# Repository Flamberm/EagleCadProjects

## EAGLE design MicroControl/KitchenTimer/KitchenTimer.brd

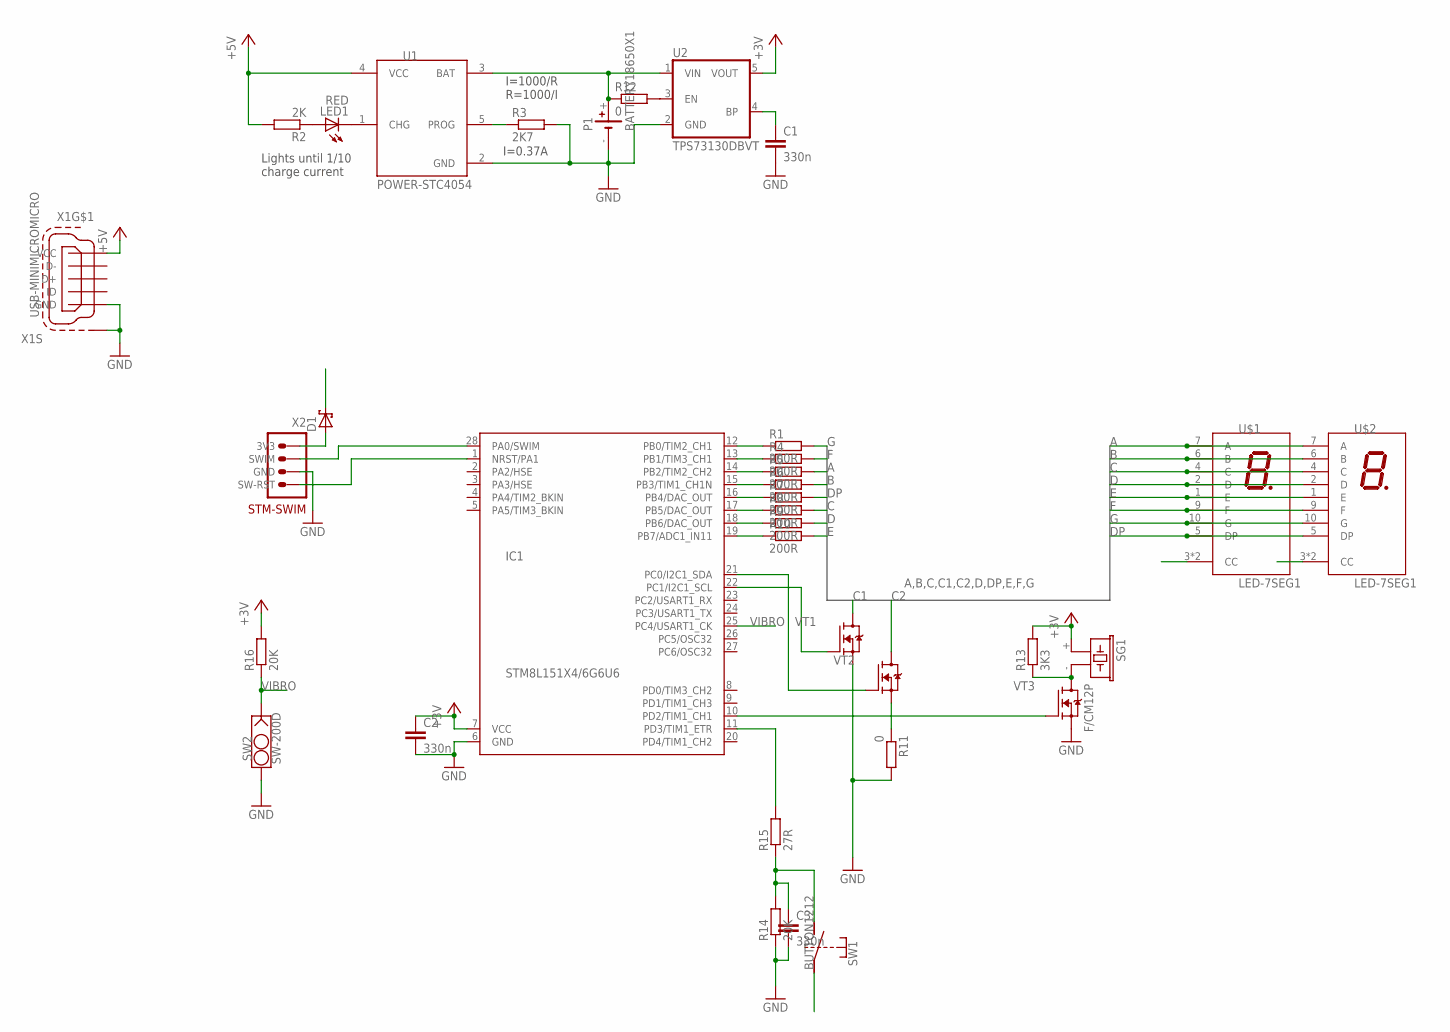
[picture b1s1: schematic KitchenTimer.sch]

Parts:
C1, C2, C3: 330n; CAP1206
D1: DIODE-SH_SOD523; SODFL1608X65
IC1: STM8L151X4/6G6U6; QFN28
LED1: RED; LED1206
P1: BATTERY18650X1; 18650X1_HOLDER
R1, R4, R5, R6, R7, R8, R9, R10: 200R; RESC2012X50
R2: 2K; RESC2012X50
R3: 2K7; RESC2012X50
R11, R12: 0; RESC2012X50
R13: 3K3; RESC3216X60
R14, R16: 20K; RESC3216X60
R15: 27R; RESC3216X60
SG1: F/CM12P
SW1: BUTTON1212; B3F-40XX
SW2: SW-200D
U1: POWER-STC4054; SOT95P280X145-5
U2: TPS73130DBVT; SOT95P280X145-5
U$1, U$2: LED-7SEG1
VT1, VT2, VT3: FET-NSOT-23; SOT95P240X115-3
X1: USB-MINIMICROMICRO; USB-B-MICRO-SMD
X2: STM-SWIMPOGOPADS; SWIM-PADS-1.27

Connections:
+3V: C2.1, D1.1 (C), IC1.7 (VCC), R13.2, R16.2, SG1.+ (1), SW1.1, SW1.2 (1), U2.5 (VOUT)
+5V: R2.2, U1.4 (VCC), X1.VBUS (VCC)
A: R5.2, U$1.7 (A), U$2.7 (A)
B: R6.2, U$1.6 (B), U$2.6 (B)
C: R8.2, U$1.4 (C), U$2.4 (C)
C1: U$1.3 (CC), U$1.8 (CC), VT1.3 (D)
C2: U$2.3 (CC), U$2.8 (CC), VT2.3 (D)
D: R9.2, U$1.2 (D), U$2.2 (D)
DP: R7.2, U$1.5 (DP), U$2.5 (DP)
E: R10.2, U$1.1 (E), U$2.1 (E)
F: R4.2, U$1.9 (F), U$2.9 (F)
G: R1.2, U$1.10 (G), U$2.10 (G)
GND: C1.2, C2.2, C3.2, IC1.6 (GND), P1.-, R3.2, R11.2, R14.1, SW2.S, U1.2 (GND), U2.2 (GND), VT1.2 (S), VT3.2 (S), X1.GND, X1.SHIELD1 (S1), X1.SHIELD2 (S1), X1.SHIELD3 (S1), X2.P$3 (GND)
unnamed: LED1.C, U1.1 (CHG)
unnamed: LED1.A, R2.1
unnamed: IC1.12 (PB0/TIM2_CH1), R1.1
unnamed: IC1.13 (PB1/TIM3_CH1), R4.1
unnamed: R3.1, U1.5 (PROG)
unnamed: IC1.14 (PB2/TIM2_CH2), R5.1
unnamed: P1.+, R12.1, U1.3 (BAT), U2.1 (VIN)
unnamed: IC1.15 (PB3/TIM1_CH1N), R6.1
unnamed: IC1.16 (PB4/DAC_OUT), R7.1
unnamed: IC1.17 (PB5/DAC_OUT), R8.1
unnamed: IC1.18 (PB6/DAC_OUT), R9.1
unnamed: IC1.19 (PB7/ADC1_IN11), R10.1
unnamed: IC1.22 (PC1/I2C1_SCL), VT1.1 (G)
unnamed: IC1.21 (PC0/I2C1_SDA), VT2.1 (G)
unnamed: R11.1, VT2.2 (S)
unnamed: R12.2, U2.3 (EN)
unnamed: C1.1, U2.4 (BP)
unnamed: R13.1, SG1.- (2), VT3.3 (D)
unnamed: IC1.10 (PD2/TIM1_CH1), VT3.1 (G)
unnamed: C3.1, R14.2, R15.1, SW1.3 (2), SW1.4 (2)
unnamed: IC1.11 (PD3/TIM1_ETR), R15.2
unnamed: IC1.28 (PA0/SWIM), X2.P$2 (SWIM)
unnamed: IC1.1 (NRST/PA1), X2.P$4 (SW-RST)
unnamed: D1.2 (A), X2.P$1 (3V3)
VIBRO: IC1.25 (PC4/USART1_CK), R16.1, SW2.G

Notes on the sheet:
I=1000/R R=1000/I
I=0.37A
Lights until 1/10 charge current

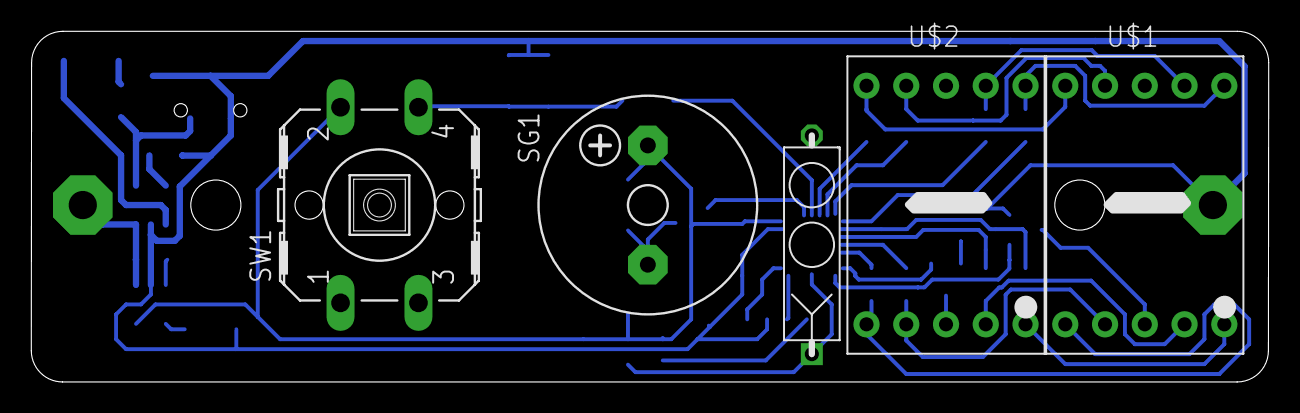
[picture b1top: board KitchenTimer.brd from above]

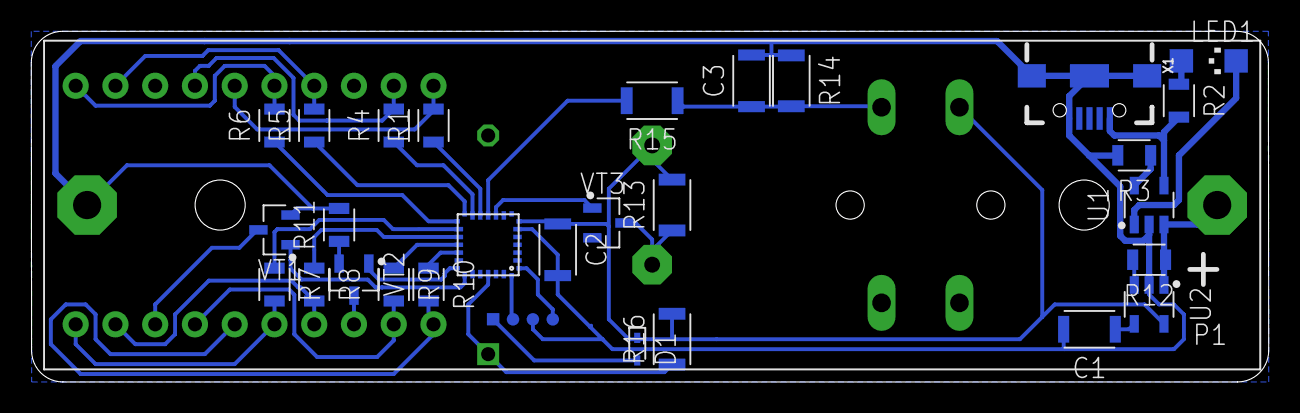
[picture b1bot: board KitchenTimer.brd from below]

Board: 2 copper layers, 79.1 x 22.4 mm, 35 parts (30 on the bottom side), 38 nets.

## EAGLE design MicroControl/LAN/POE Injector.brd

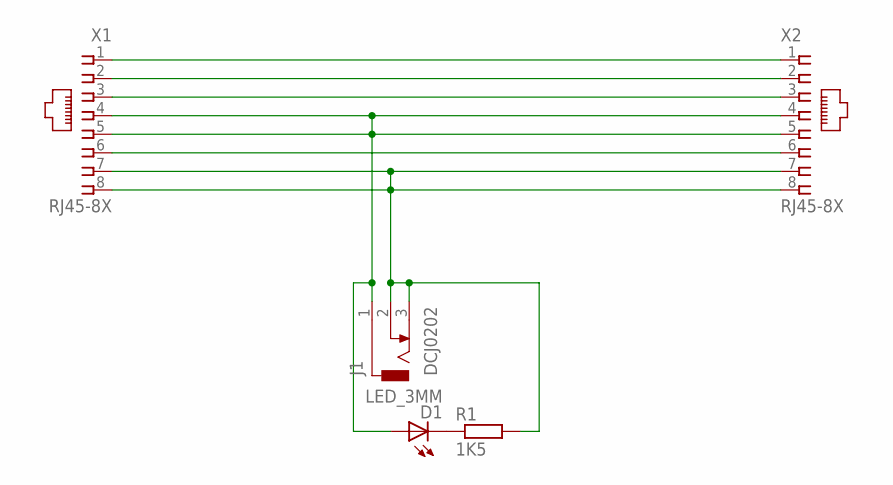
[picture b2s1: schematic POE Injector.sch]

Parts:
D1: LED_3MM; LED3MM
J1: DCJ0202
R1: 1K5; R1206
X1, X2: RJ45-8X; RJ45-NO-SHIELD

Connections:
unnamed: X1.1, X2.1
unnamed: X1.2, X2.2
unnamed: X1.3, X2.3
unnamed: X1.6, X2.6
unnamed: J1.2, J1.3, R1.2, X1.7, X1.8, X2.7, X2.8
unnamed: D1.A, J1.1, X1.4, X1.5, X2.4, X2.5
unnamed: D1.K (C), R1.1

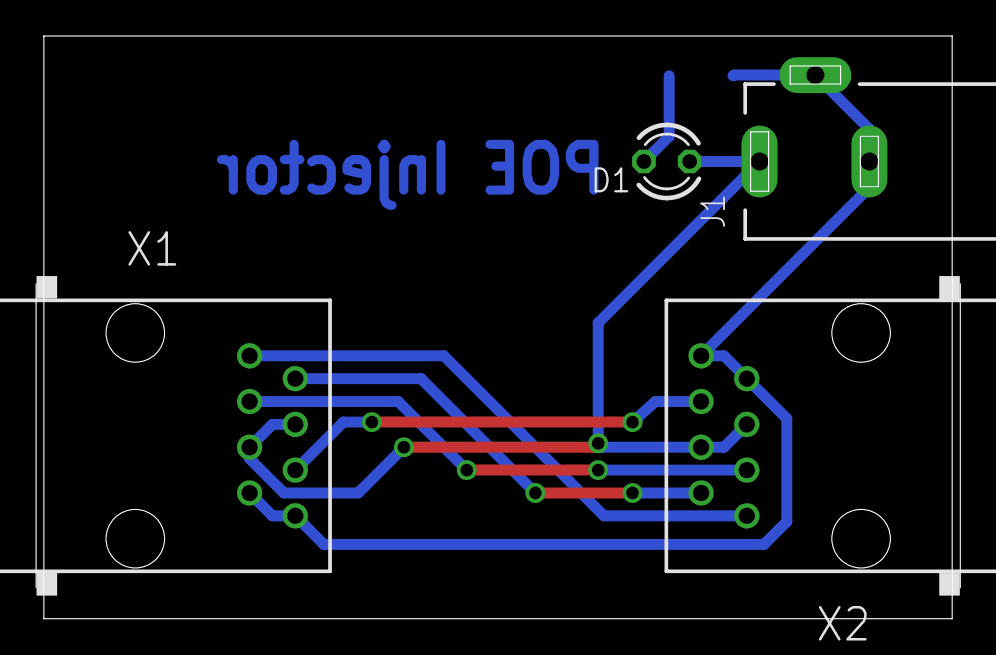
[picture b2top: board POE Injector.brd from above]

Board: 2 copper layers, 50.5 x 32.4 mm, 5 parts (1 on the bottom side), 7 nets.

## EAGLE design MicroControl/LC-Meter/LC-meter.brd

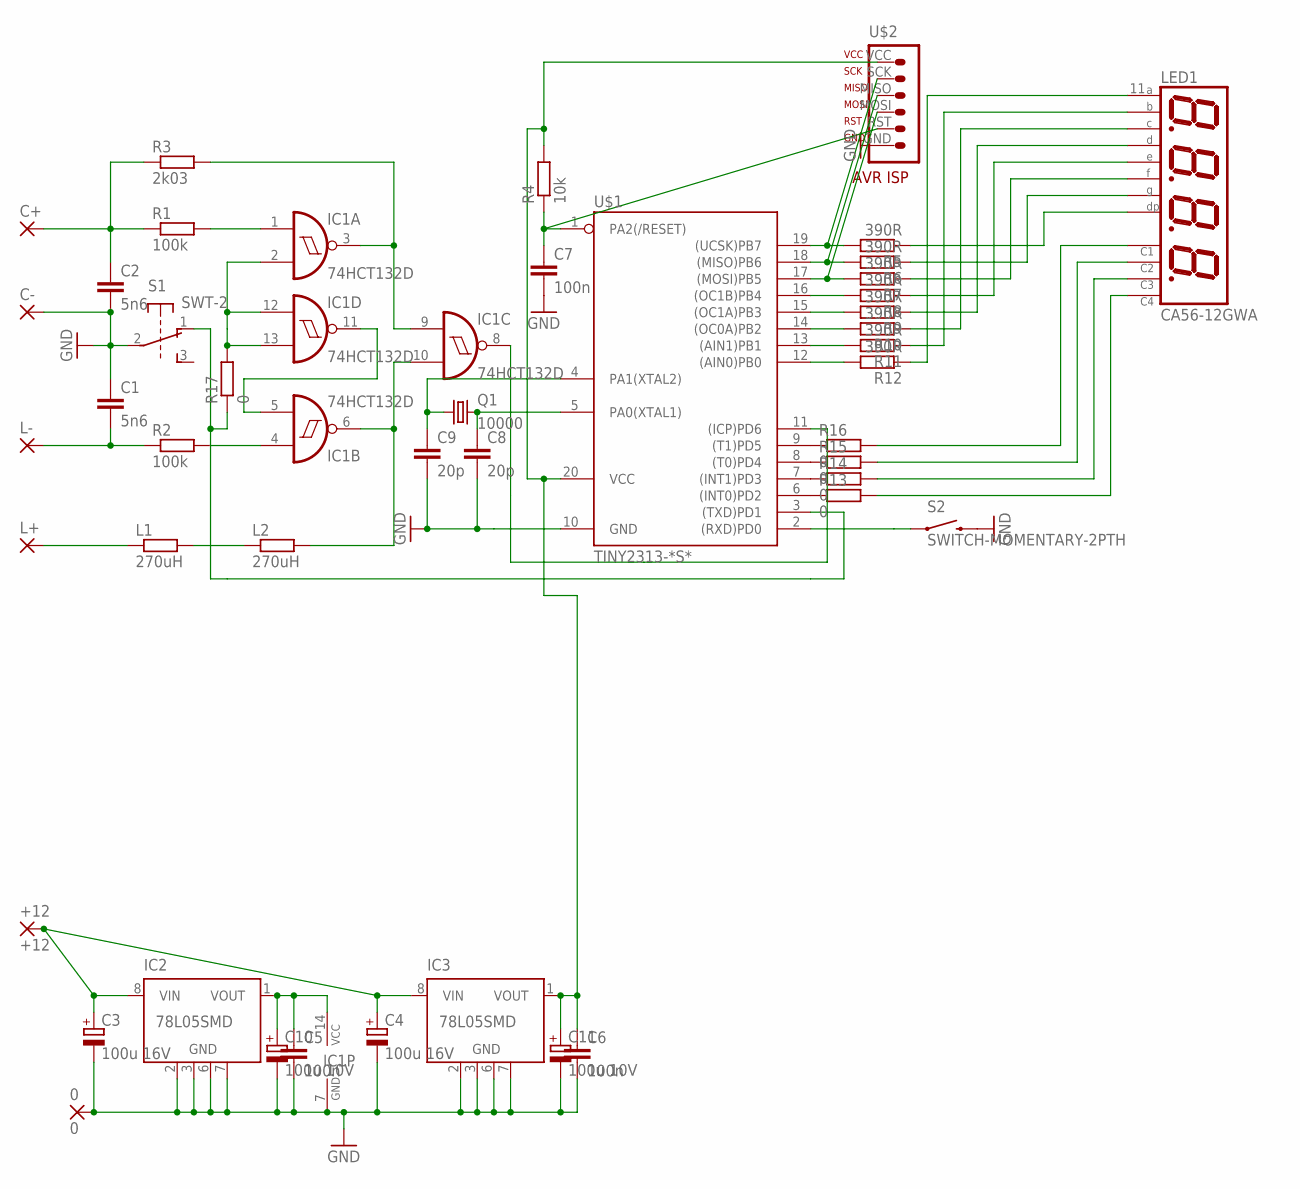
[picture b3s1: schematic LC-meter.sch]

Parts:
0: 0; 3,17/1,1
+12: +12; 3,17/1,1
C1, C2: 5n6; C0805
C3, C4: 100u 16V; E2,5-7
C5, C6, C7: 100n; C0805
C8, C9: 20p; C1206
C10, C11: 100u 10V; E2,5-7
C+: 3,17/1,1
C-: 3,17/1,1
IC1: 74HCT132D; SO14
IC2, IC3: 78L05SMD; SO08
L1, L2: 270uH; R1210
L+: 3,17/1,1
L-: 3,17/1,1
LED1: CA56-12GWA; 0,56_4X7SEG_LED
Q1: 10000; HC49/S
R1, R2: 100k; R1206
R3: 2k03; R1206
R4: 10k; R1206
R5, R6, R7, R8, R9, R10, R11, R12: 390R; R1206
R13, R14, R15, R16, R17: 0; R1206
S1: SWT-2
S2: SWITCH-MOMENTARY-2PTH; TACTILE-PTH
U$1: TINY2313-*S*; SO20L$
U$2: AVR-ISP-6-ROW

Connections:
GND: 0.1, C1.1, C2.2, C3.-, C4.-, C5.2, C6.2, C7.2, C8.2, C9.2, C10.-, C11.-, C-.1, IC1.7 (GND), IC2.2 (GND), IC2.3 (GND), IC2.6 (GND), IC2.7 (GND), IC3.2 (GND), IC3.3 (GND), IC3.6 (GND), IC3.7 (GND), S1.2, S2.3 (2), U$1.10 (GND), U$2.GND
unnamed: IC1.8 (O), U$1.11 ((ICP)PD6)
unnamed: R17.1, S1.1, U$1.3 ((TXD)PD1)
unnamed: IC1.5 (I1), IC1.11 (O)
unnamed: IC1.6 (O), IC1.10 (I1), L2.2
unnamed: IC1.3 (O), IC1.9 (I0), R3.2
unnamed: IC1.1 (I0), R1.2
unnamed: IC1.4 (I0), R2.2
unnamed: C1.2, L-.1, R2.1
unnamed: C2.1, C+.1, R1.1, R3.1
unnamed: L1.1, L+.1
unnamed: L1.2, L2.1
unnamed: +12.1, C3.+, C4.+, IC2.8 (VIN), IC3.8 (VIN)
unnamed: R5.2, U$1.19 ((UCSK)PB7), U$2.SCK
unnamed: R13.1, U$1.6 ((INT0)PD2)
unnamed: C6.1, C11.+, IC3.1 (VOUT), R4.2, U$1.20 (VCC), U$2.VCC
unnamed: C5.1, C10.+, IC1.14 (VCC), IC2.1 (VOUT)
unnamed: R6.2, U$1.18 ((MISO)PB6), U$2.MISO
unnamed: C7.1, R4.1, U$1.1 (PA2(/RESET)), U$2.RST
unnamed: C8.1, Q1.2, U$1.5 (PA0(XTAL1))
unnamed: C9.1, Q1.1, U$1.4 (PA1(XTAL2))
unnamed: S2.1, U$1.2 ((RXD)PD0)
unnamed: R7.2, U$1.17 ((MOSI)PB5), U$2.MOSI
unnamed: R8.2, U$1.16 ((OC1B)PB4)
unnamed: R9.2, U$1.15 ((OC1A)PB3)
unnamed: R10.2, U$1.14 ((OC0A)PB2)
unnamed: R11.2, U$1.13 ((AIN1)PB1)
unnamed: R12.2, U$1.12 ((AIN0)PB0)
unnamed: LED1.11 (A), R12.1
unnamed: LED1.7 (B), R11.1
unnamed: LED1.4 (C), R10.1
unnamed: LED1.2 (D), R9.1
unnamed: LED1.1 (E), R8.1
unnamed: LED1.10 (F), R7.1
unnamed: LED1.5 (G), R6.1
unnamed: LED1.3 (DP), R5.1
unnamed: LED1.12 (A1), R16.2
unnamed: LED1.9 (A2), R15.2
unnamed: LED1.8 (A3), R14.2
unnamed: LED1.6 (A4), R13.2
unnamed: R14.1, U$1.7 ((INT1)PD3)
unnamed: R15.1, U$1.8 ((T0)PD4)
unnamed: R16.1, U$1.9 ((T1)PD5)
unnamed: IC1.2 (I1), IC1.12 (I0), IC1.13 (I1), R17.2

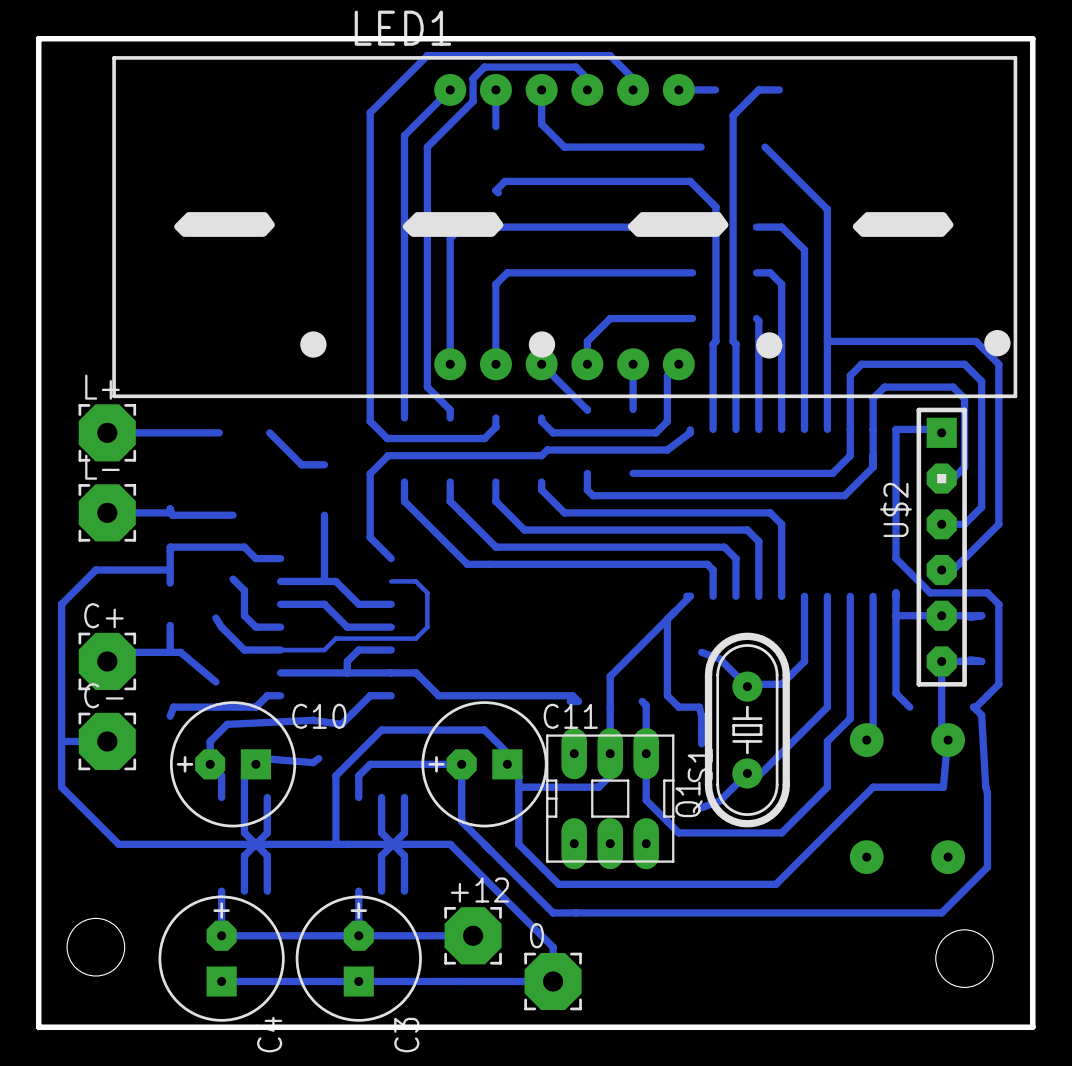
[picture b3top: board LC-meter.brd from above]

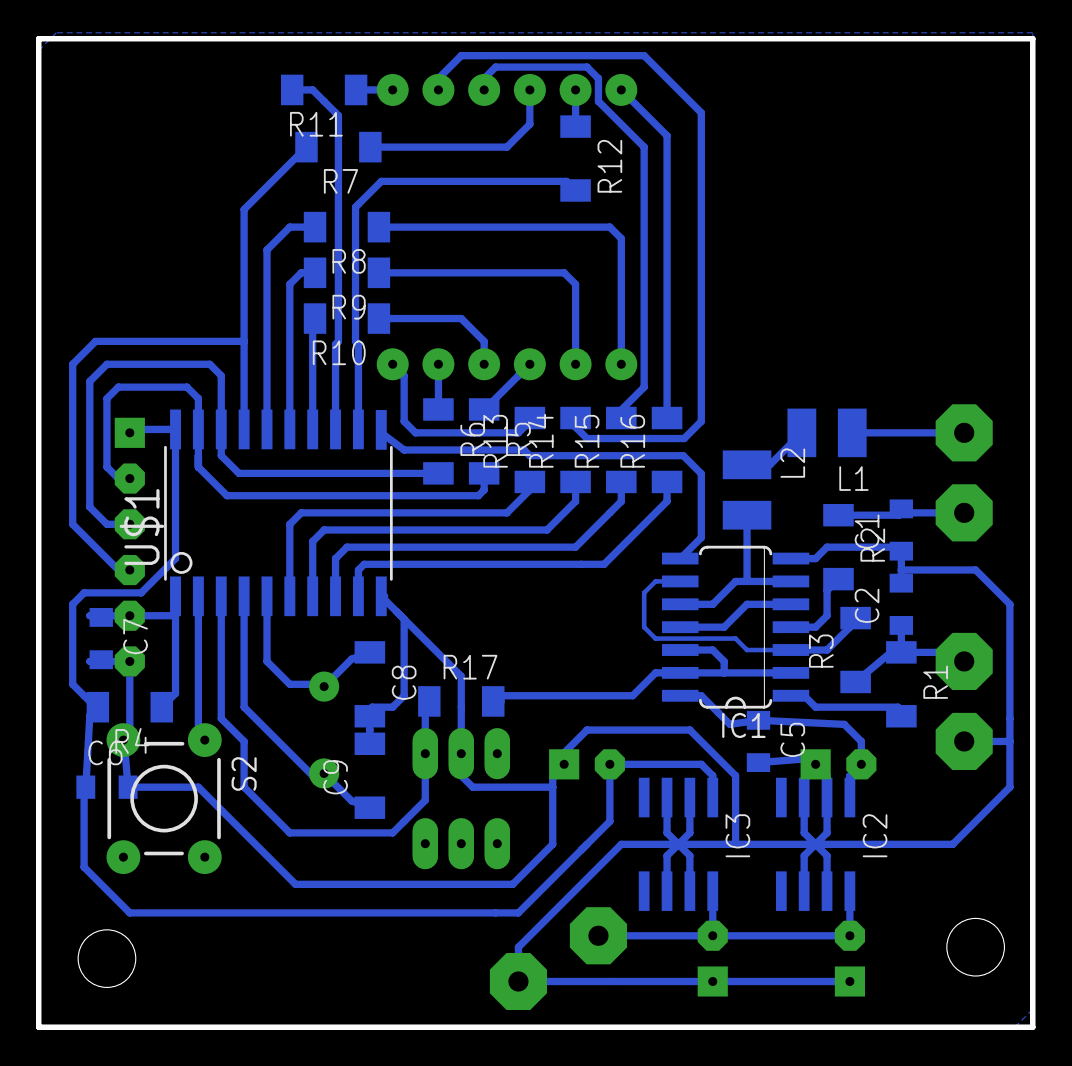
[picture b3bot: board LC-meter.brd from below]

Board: 2 copper layers, 55.2 x 54.9 mm, 45 parts (31 on the bottom side), 44 nets.

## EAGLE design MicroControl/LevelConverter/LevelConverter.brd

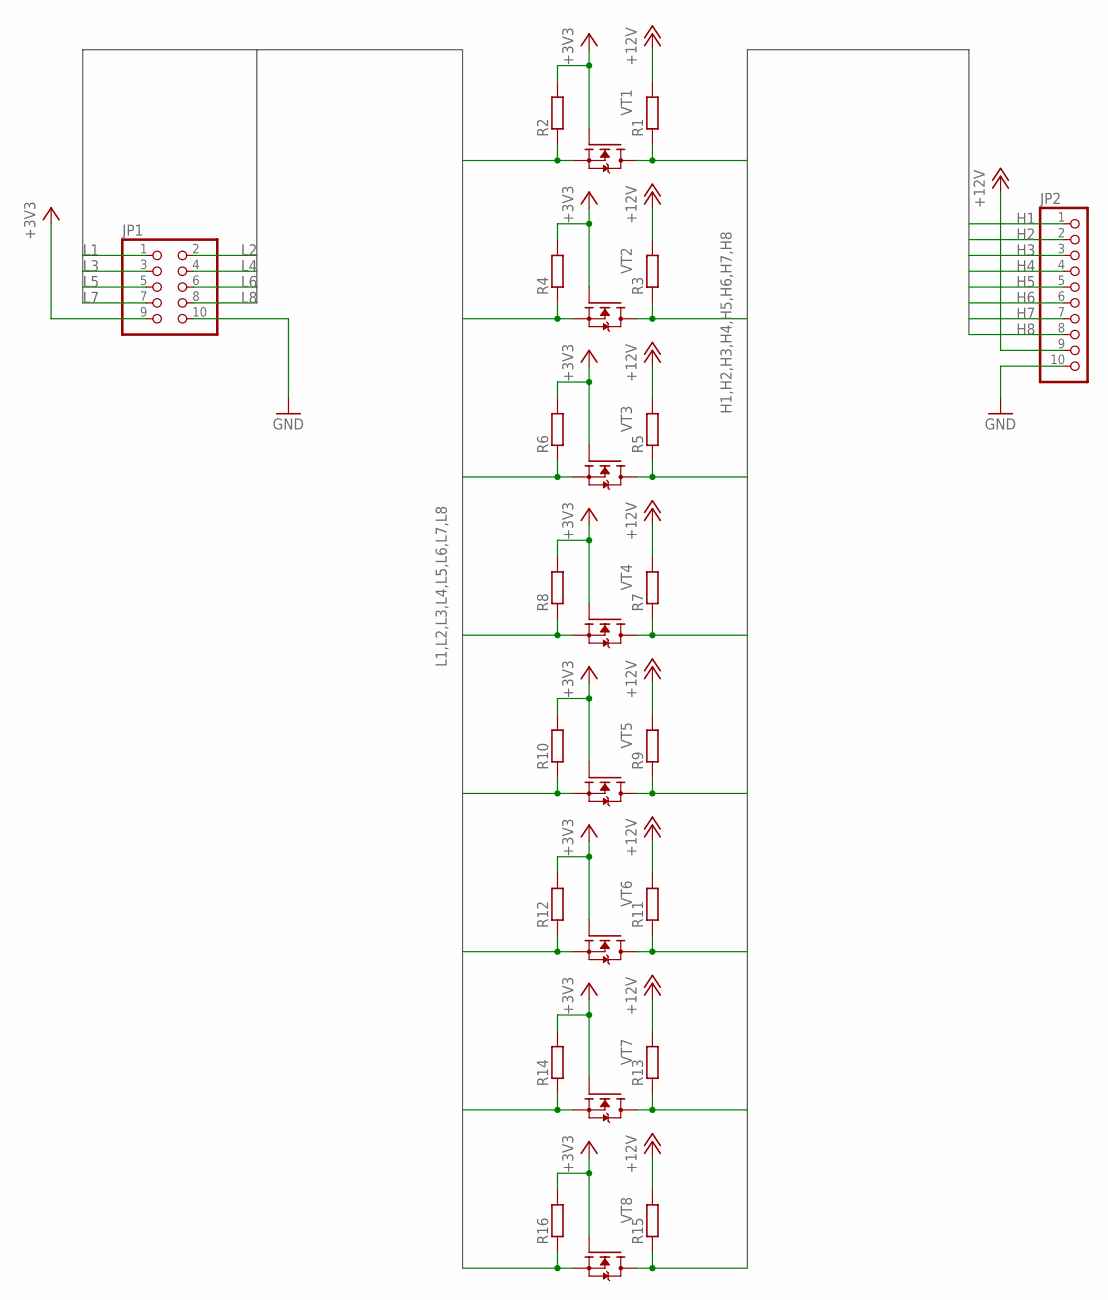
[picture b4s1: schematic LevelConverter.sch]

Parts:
JP1: PINHD-2X5/90; 2X05/90
JP2: PINHD-1X10; 1X10
R1, R2, R3, R4, R5, R6, R7, R8, R9, R10, R11, R12, R13, R14, R15, R16: R_R0805; RESC2012X50
VT1, VT2, VT3, VT4, VT5, VT6, VT7, VT8: FET-NSOT-23; SOT95P240X115-3

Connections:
+3V3: JP1.9, R2.2, R4.2, R6.2, R8.2, R10.2, R12.2, R14.2, R16.2, VT1.1 (G), VT2.1 (G), VT3.1 (G), VT4.1 (G), VT5.1 (G), VT6.1 (G), VT7.1 (G), VT8.1 (G)
+12V: JP2.9, R1.2, R3.2, R5.2, R7.2, R9.2, R11.2, R13.2, R15.2
GND: JP1.10, JP2.10
H1: JP2.1, R1.1, VT1.3 (D)
H2: JP2.2, R3.1, VT2.3 (D)
H3: JP2.3, R5.1, VT3.3 (D)
H4: JP2.4, R7.1, VT4.3 (D)
H5: JP2.5, R9.1, VT5.3 (D)
H6: JP2.6, R11.1, VT6.3 (D)
H7: JP2.7, R13.1, VT7.3 (D)
H8: JP2.8, R15.1, VT8.3 (D)
L1: JP1.1, R2.1, VT1.2 (S)
L2: JP1.2, R4.1, VT2.2 (S)
L3: JP1.3, R6.1, VT3.2 (S)
L4: JP1.4, R8.1, VT4.2 (S)
L5: JP1.5, R10.1, VT5.2 (S)
L6: JP1.6, R12.1, VT6.2 (S)
L7: JP1.7, R14.1, VT7.2 (S)
L8: JP1.8, R16.1, VT8.2 (S)

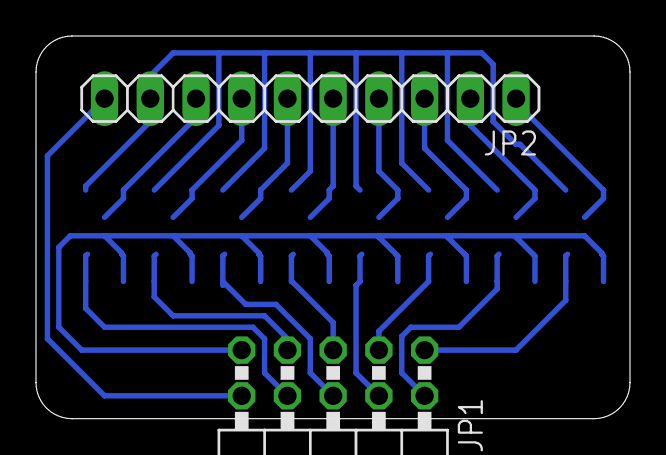
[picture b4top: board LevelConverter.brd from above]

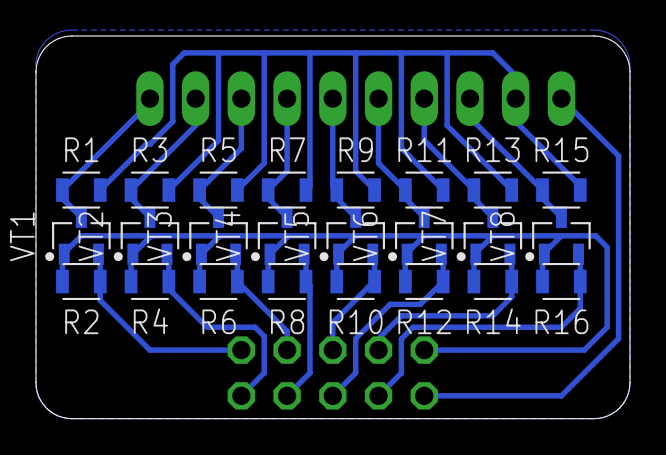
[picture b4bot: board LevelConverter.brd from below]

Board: 2 copper layers, 33.0 x 21.3 mm, 26 parts (24 on the bottom side), 19 nets.

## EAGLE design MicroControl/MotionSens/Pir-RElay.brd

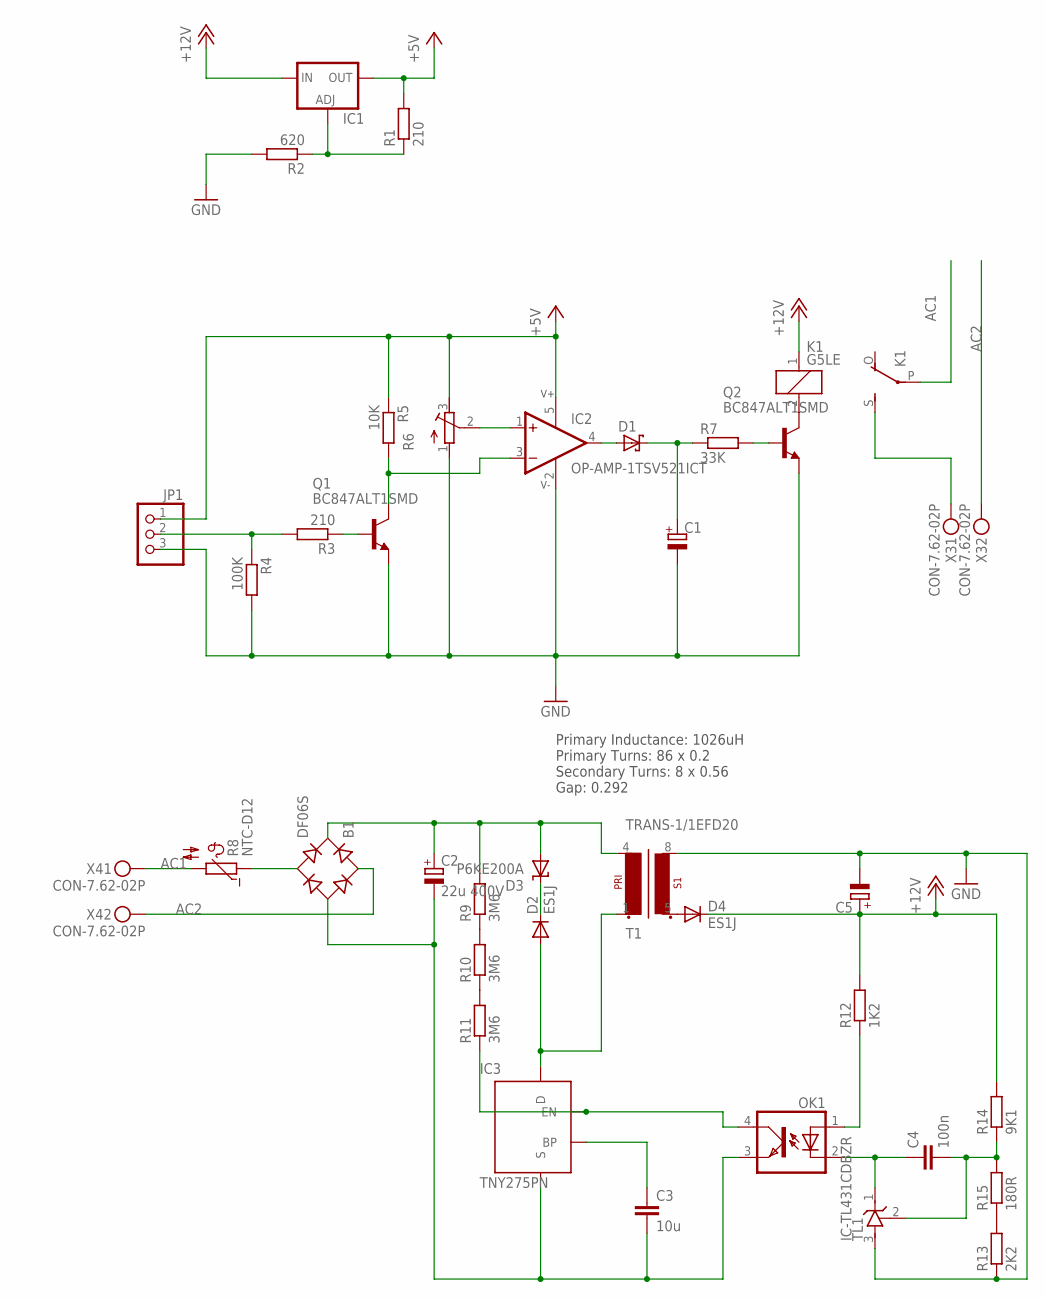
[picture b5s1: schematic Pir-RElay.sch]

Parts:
B1: DF06S; DFS
C1: CAP-POL_E2.5-7; E2,5-7
C2: 22u 400V; E5-13
C3: 10u; C1210
C4: 100n; C0805
C5: CPOL-EUE7.5-18; E7,5-18
D1: DIODE-SH_SOD523; SODFL1608X65
D2, D4: ES1J; DO214AC
D3: P6KE200A; DO15-12
IC1: VREG-ADJLD1117S; SOT230P700X180-4
IC2: OP-AMP-1TSV521ICT; SC70-5L
IC3: TNY275PN; DIP-8C
JP1: PINHD-1X3/90; 1X03/90
K1: G5LE
OK1: OPTOTRANSPC817; DIL04
Q1, Q2: BC847ALT1SMD; SOT23
R1, R3: 210; RESC2012X50
R2: 620; RESC2012X50
R4: 100K; RESC2012X50
R5: 10K; RESC2012X50
R6: R_POT3296X; POT-3296X
R7: 33K; RESC2012X50
R8: NTC-D12
R9, R10, R11: 3M6; R0805
R12: 1K2; R1206
R13: 2K2; RESC2012X50
R14: 9K1; R1206
R15: 180R; R1206
T1: TRANS-1/1EFD20; EFD20_8PIN
TL1: IC-TL431CDBZR; SOT23
X3, X4: CON-7.62-02P; KF25C-7.62-02P-13

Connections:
+5V: IC1.2 (OUT), IC1.4 (OUT), IC2.5 (V+), JP1.1, R1.2, R5.1, R6.3 (E)
+12V: C5.+, D4.C, IC1.3 (IN), K1.1, R12.2, R14.2
AC1: K1.P, R8.2, X4.P$1
AC2: B1.AC1, X3.P$2, X4.P$2
GND: C1.-, C5.-, IC2.2 (V-), JP1.3, Q1.2 (E), Q2.2 (E), R2.2, R4.2, R6.1 (A), R13.1, T1.8 (S1-2), TL1.3 (A)
unnamed: IC1.1 (ADJ), R1.1, R2.1
unnamed: B1.AC2, R8.1
unnamed: K1.S, X3.P$1
unnamed: Q2.1 (B), R7.2
unnamed: JP1.2, R3.2, R4.1
unnamed: Q1.1 (B), R3.1
unnamed: IC2.3 (-IN), Q1.3 (C), R5.2
unnamed: IC2.1 (+IN), R6.2 (S)
unnamed: D1.2 (A), IC2.4 (OUT)
unnamed: C1.+, D1.1 (C), R7.1
unnamed: K1.2, Q2.3 (C)
unnamed: B1.+, C2.+, D3.A, R9.2, T1.4 (P1-2)
unnamed: B1.-, C2.-, C3.2, IC3.5 (S), IC3.6 (S), IC3.7 (S), IC3.8 (S), OK1.3 (EMIT)
unnamed: C3.1, IC3.2 (BP)
unnamed: D2.A, IC3.4 (D), T1.1 (P1-1)
unnamed: D2.C, D3.C
unnamed: IC3.1 (EN), OK1.4 (COL), R11.1
unnamed: R9.1, R10.2
unnamed: R10.1, R11.2
unnamed: D4.A, T1.5 (S1-1)
unnamed: OK1.1 (A), R12.1
unnamed: C4.1, OK1.2 (C), TL1.1 (C)
unnamed: C4.2, R14.1, R15.2, TL1.2 (R)
unnamed: R13.2, R15.1

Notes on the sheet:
Primary Inductance: 1026uH Primary Turns: 86 x 0.2 Secondary Turns: 8 x 0.56 Gap: 0.292

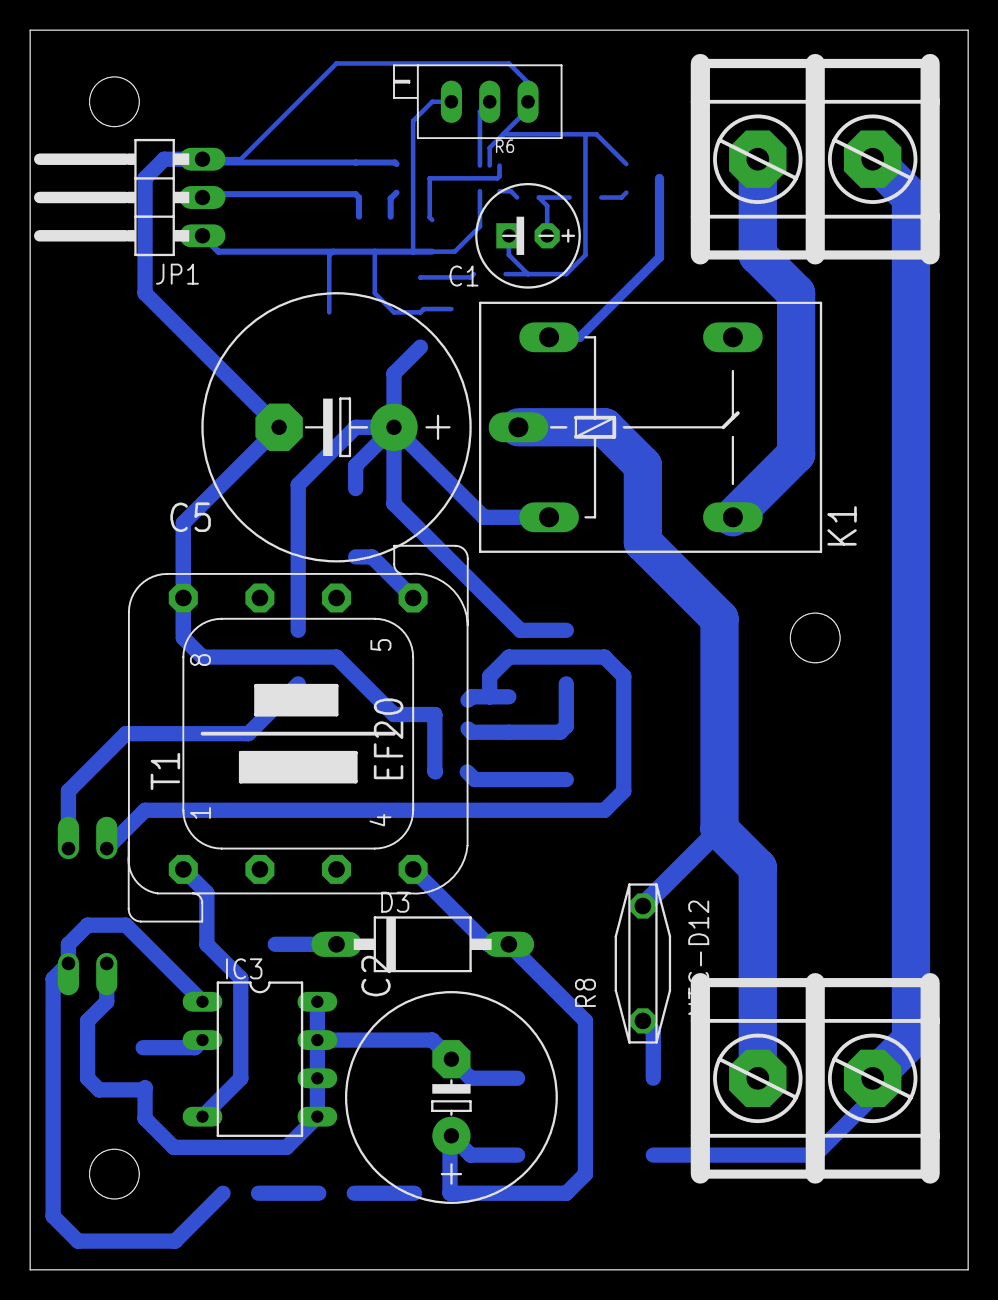
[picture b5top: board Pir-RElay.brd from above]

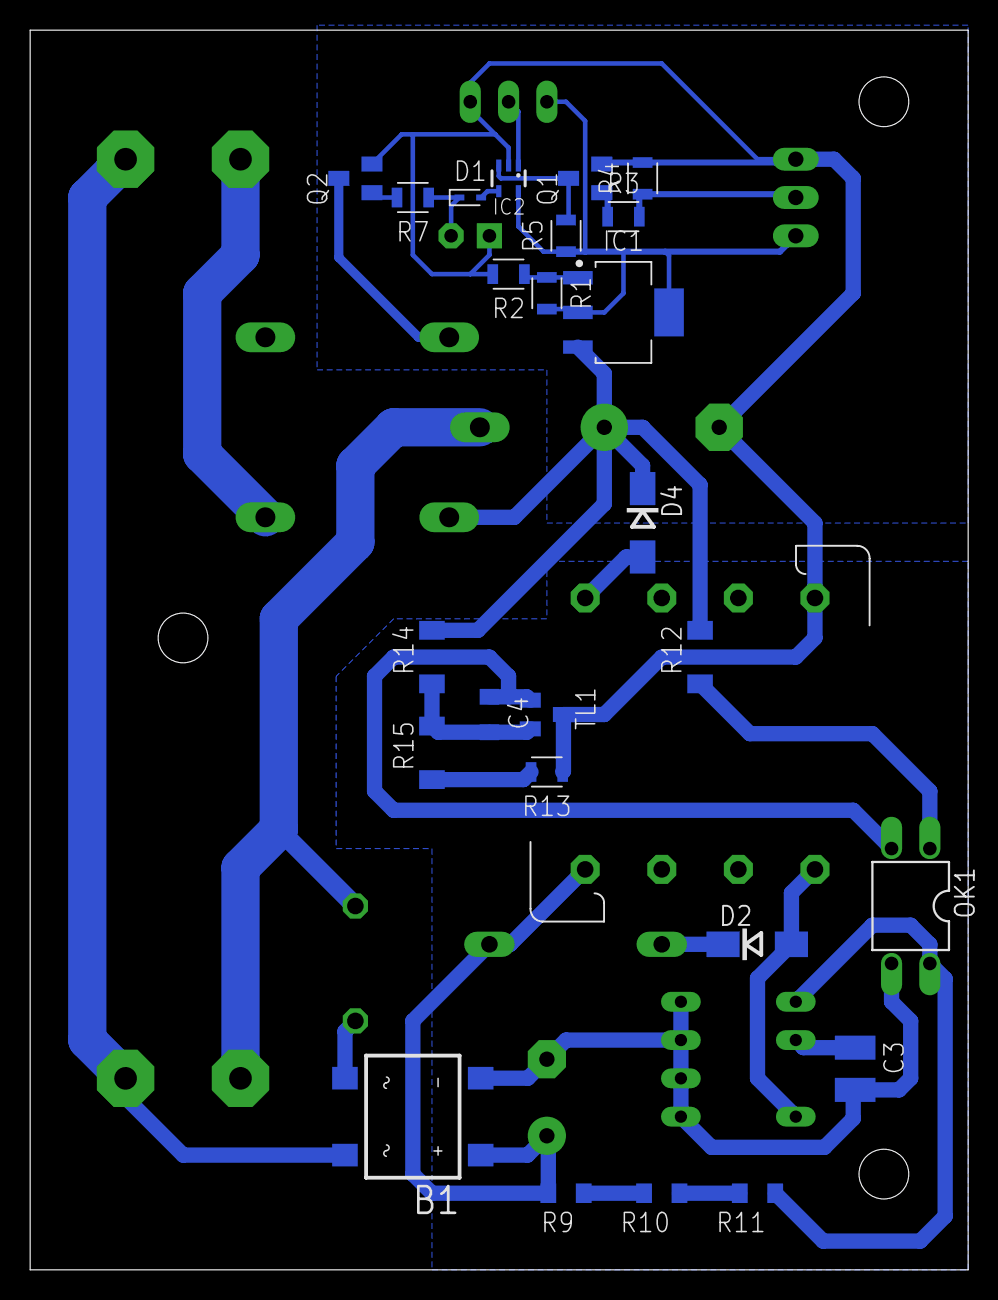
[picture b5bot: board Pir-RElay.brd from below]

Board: 2 copper layers, 62.2 x 82.2 mm, 37 parts (25 on the bottom side), 29 nets.

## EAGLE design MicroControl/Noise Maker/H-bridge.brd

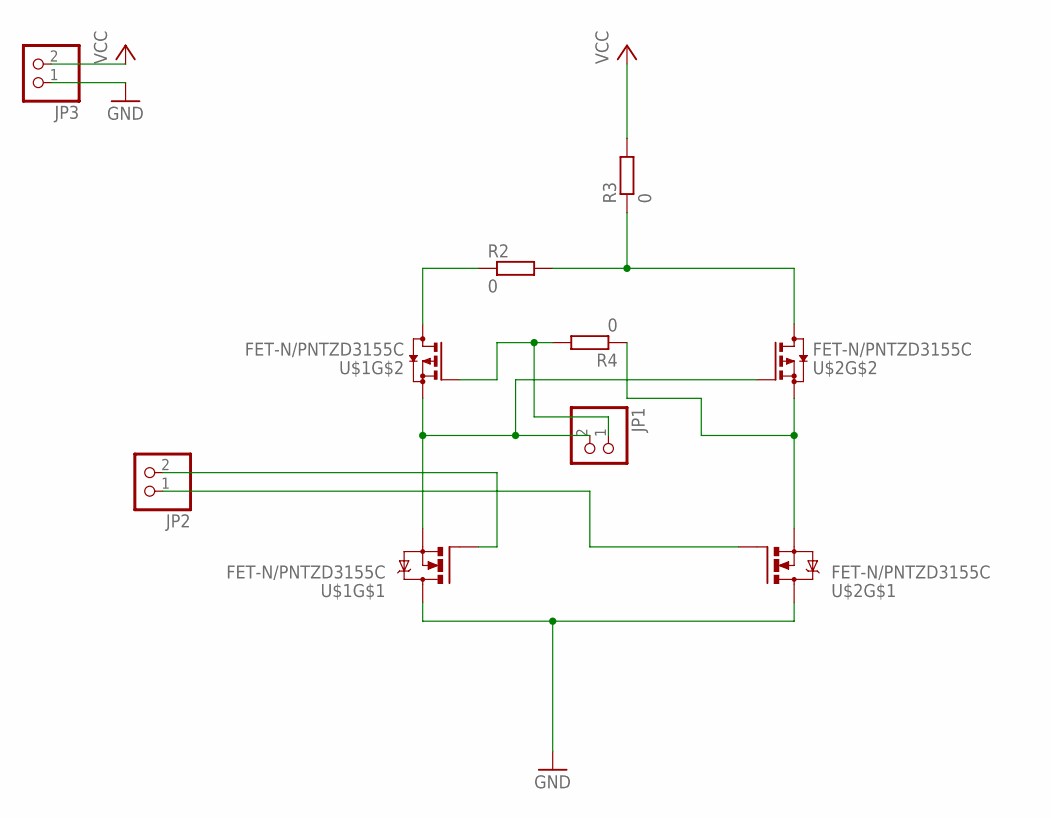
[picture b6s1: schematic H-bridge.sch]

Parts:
JP1, JP2, JP3: PINHD-1X2; 1X02
R2, R3, R4: 0; R0805
U$1, U$2: FET-N/PNTZD3155C; SOT-563

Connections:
GND: JP3.1, U$1.6 (D), U$2.6 (D)
unnamed: R4.1, U$2.1 (S), U$2.4 (S)
unnamed: JP1.2, U$1.1 (S), U$1.4 (S), U$2.5 (G)
unnamed: JP2.1, U$2.2 (G)
unnamed: R2.1, U$1.3 (D)
unnamed: R2.2, R3.1, U$2.3 (D)
unnamed: JP1.1, R4.2, U$1.5 (G)
unnamed: JP2.2, U$1.2 (G)
VCC: JP3.2, R3.2

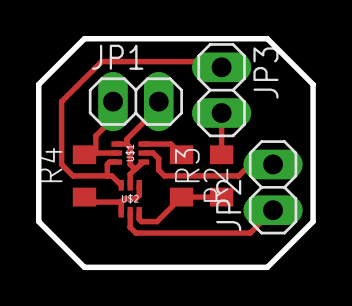
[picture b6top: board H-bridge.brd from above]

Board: 2 copper layers, 15.2 x 12.7 mm, 8 parts (0 on the bottom side), 9 nets.

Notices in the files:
parts and their libraries:
SparkFun-Electromechanical: Licensing: Creative Commons ShareAlike 4.0 International - https://creativecommons.org/licenses/by-sa/4.0
